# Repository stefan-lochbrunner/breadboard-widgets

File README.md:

A collection of widgets/adapters/breakouts to make prototyping easier.
For more infos please see [**project page on HaD.io**](https://hackaday.io/project/6332-breadboard-widgets). A panel with a subset of these booards can also be ordered from the [**DirtyPCBs store**](http://dirtypcbs.com/view.php?share=9791&accesskey=ab0e86ffb8323f031e5f15a2c98e4056)

#### ATtiny prog board
Programming board suitable for ATtiny45/85 microcontrollers. Plugs into a breadboards power rails to minimize required space.
USB version pin compatible with uUSB breakout.
[**more info**](https://hackaday.io/project/6332-breadboard-widgets/log/19613-attiny-prog-board)

##### Standard:

##### With USB:

#### DBx breakout
Simple breakout for DA-15, DB/DE-9 & DE-15(VGA) connectors. DB-9 to be placed on DA-15 footprint. [**more info**](https://hackaday.io/project/6332/log/26554)

#### ISP breakout
Simple ISP breakout. Order of pins corresponds to ATmega328 DIP so breakout can be plugged in next to it. Jumper wire required for RST. Also fits ATtiny45/85 with additional jumper for GND.
[**more info**](https://hackaday.io/project/6332-breadboard-widgets/log/19660-isp-breakout)

##### v1.2

Added two additional pins to ISP & breadboard headers to allow this board to be used as breakout for e.g. ESP-01's.

#### MOSFET breakout
DPAK MOSFET breakout to be used as single channel PWM driver. Footprint should also fit SOT-223 package where pin 2 is internally connected to tab.
[**more info**](https://hackaday.io/project/6332-breadboard-widgets/log/21781-mosfet-breakout-for-pwm-driver)

#### SMD LED breakout
Straight forward SMD LED breakout. See also [**revised button board that can be used as LED breakout**](https://github.com/stefan-lochbrunner/breadboard-widgets/tree/master/button)

##### single

##### multi

#### SOIC/TSSOP-16 breakout & protoboard
Some variations on a SOIC-16 and TSSOP-16 breakout board.

#### USB breakouts

##### uUSB breakout
Main functionality is to provide "VUSB circuitry" for AVR microcontrollers. Can also be used as generic uUSB breakout by shorting 68R resistor footprints or as breadboard power supply (supplying 5V).
[**more info**](https://hackaday.io/project/6332-breadboard-widgets/log/19615-uusb-breakout)

###### v1

###### v2
Allows for supplying different voltages by populating the bottom side with desired regulator. For 5V short solder jumper.

superseded by v3

###### v3
Allows for supplying different voltages by populating the bottom side with desired regulator. The following modes are possible:

- Supply rail and Vcc pin with 5V directly from USB (regulator not populated, short all 3 pads of solder jumper)
- Supply regulator with 5V from USB which in turn supplies rail and Vcc pin (short center and top pad)
- Supply regulator from rail and get regulated voltage on Vcc pin (short center and bottom pad)

##### USB-B

#### Audio breakouts
Breakout boards for 3.5mm TRS & RCA jacks. [**more info**](https://hackaday.io/project/6332-breadboard-widgets/log/21029-sufs-audio-breakouts)

Based on @sufzoli 's https://github.com/sufzoli/suf-electronics-breadboard

Combined both into single board to save PCB space.

#### Button w/ pull resistor
[**more info**](https://hackaday.io/project/6332-breadboard-widgets/log/19614-button-w-pull-updown)

##### single button
Small board that incorporates a button and pull-resistor. Can be plugged into power rails. Depending on which side of a breadboard it is plugged in, acts as pull-up or pull-down. Optional footprints for low-pass filter for debouncing.

##### single button with SMD LED breakout
added over complicated LED breakout to utilize board space. Also added arrow to indicate pull direction.

#### Negative voltage converter
Included files of @sufzoli 's [**voltage inverter**](https://github.com/sufzoli/suf-electronics-USB-INV-PM) here and remade in Eagle for coherency. [**more info**](https://hackaday.io/project/6332-breadboard-widgets/log/22127-sufs-negative-voltage-converter)

Based on ICL7660, inverts supply voltage.

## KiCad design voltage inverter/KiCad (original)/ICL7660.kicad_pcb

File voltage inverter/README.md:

Included @sufzoli 's [**voltage inverter**](https://github.com/sufzoli/suf-electronics-USB-INV-PM) here and remade in Eagle for coherency. [**more info**](https://hackaday.io/project/6332-breadboard-widgets/log/22127-sufs-negative-voltage-converter)

Based on ICL7660, inverts supply voltage.

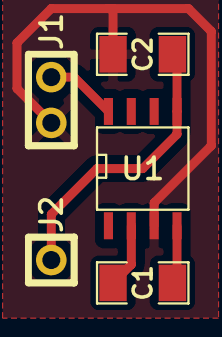
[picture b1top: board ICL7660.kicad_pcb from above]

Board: 2 copper layers, 5 parts (0 on the bottom side), 5 nets.

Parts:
C1, C2: 10uF/16V; SM1206
J1: PWR; HDR-2
J2: OUT; HDR-1
U1: ICL7660S; SOIC-8

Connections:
GND: C2.2, J1.2, U1.3
unnamed: C1.1, U1.2
unnamed: C1.2, U1.4
unnamed: C2.1, J2.1, U1.5
VCC: J1.1, U1.8

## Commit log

2015-05-23 :neckbeard: Added .gitattributes & .gitignore files
2015-05-23 Added ATtiny programming board
2015-05-23 added button w/ pull-resistor
2015-05-23 added uUSB breakout
2015-05-23 added prog board readme
2015-05-23 added readme
2015-06-16 updated project link in readme
2015-06-16 added ISPbreadboardAdapter
2015-06-17 updated readme w/ images
2015-06-20 added some info to silk screen
2015-06-20 updated images of brd files
2015-06-21 added single_button-dual_LED
2015-06-21 updated sch.png
2015-06-23 updated .brd
2015-06-23 added SMD LED breakout
2015-06-24 added uUSB breakout v3 to replace v2
2015-06-24 removed uUSB breakout v2
2015-07-16 merged @sufzoli 's suf-electronics-breadboard repo & restructured content
2015-07-16 added images
2015-07-29 added multi LED and MOSFET breakout
2015-07-29 changed file names
2015-08-04 added voltage inverter
2015-08-04 updated brd & images
2015-10-09 added DBx breakout
2015-10-12 updated board
2015-10-12 updated brd
2015-10-12 updated images
2015-10-18 added SMD breakout & proto board
2015-10-18 renamed boards image
2015-11-05 added ISP breakout v1.1
2015-11-15 added ISBbreadboardAdapter v1.2
2015-12-11 updated ATtiny prog board with USB
2015-12-11 updated brd image
2016-01-05 added ICL7669 v3
2016-01-06 added SOIC_TSSOP-20 boards
2016-01-20 added TSOP-II-44 breakout
2016-01-20 added TSOP-II-44_v2 with minor changes
2016-01-21 added TSOP-II-44_v3 with SRAM pinout
2016-01-22 test
2016-01-23 swapped supply pins
2016-01-24 added ISP breakout v1.2.1
2016-01-24 added UART matrix
2016-07-31 added MCP16252 boost regulator board
2016-10-09 added prog board BOM
2016-10-09 updated prog board BOM
2016-10-09 added boost regulator BOM
2016-10-09 updated boost regulator BOM
2016-10-09 added button BOM
2016-10-09 updated button BOM
2016-10-09 added more BOMs
2022-07-19 Added WS2812B breakout
2022-12-12 Added USB-C 2.0 breakout
2022-12-12 Updated ATtiny prog board README.md.
2022-12-12 Updated uUSB breakout README.md
2022-12-12 Added USB-C breakout README.md
2022-12-12 Updated ATtiny prog board README.md
2022-12-12 Updated USB-C breakout README.md
2022-12-12 Updated ISP breadboard adapter README.md
2022-12-12 Updated SMD LED breakout README.md
